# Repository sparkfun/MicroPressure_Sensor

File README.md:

# SparkFun MicroPressure Sensor

========================================

[*SparkFun MicroPressure Sensor (16476)*](https://www.sparkfun.com/products/16476)

<Basic description of the part.>

Repository Contents
-------------------

* **/Documentation** - Data sheets, additional product information
* **/Hardware** - Eagle design files (.brd, .sch)
* **/Libraries** - Libraries for use with the <PRODUCT NAME>
* **/Production** - Production panel files (.brd)
* **/Software** - Related software for the <PRODUCT NAME>

Documentation
-------------
* **[Library](https://github.com/sparkfun/SparkFun_MPR_Arduino_Library)** - Arduino library for the SparkFun MicroPressure Sensor.
* **[Hookup Guide](https://learn.sparkfun.com/tutorials/sparkfun-qwiic-micropressure-hookup-guide)** - Basic hookup guide for the SparkFun Qwiic MicroPressure Sensor.

License Information
-------------------

This product is _**open source**_! 

Please review the LICENSE.md file for license information. 

If you have any questions or concerns on licensing, please contact technical support on our [SparkFun forums](https://forum.sparkfun.com/viewforum.php?f=152).

Distributed as-is; no warranty is given.

- Your friends at SparkFun.

_<COLLABORATION CREDIT>_

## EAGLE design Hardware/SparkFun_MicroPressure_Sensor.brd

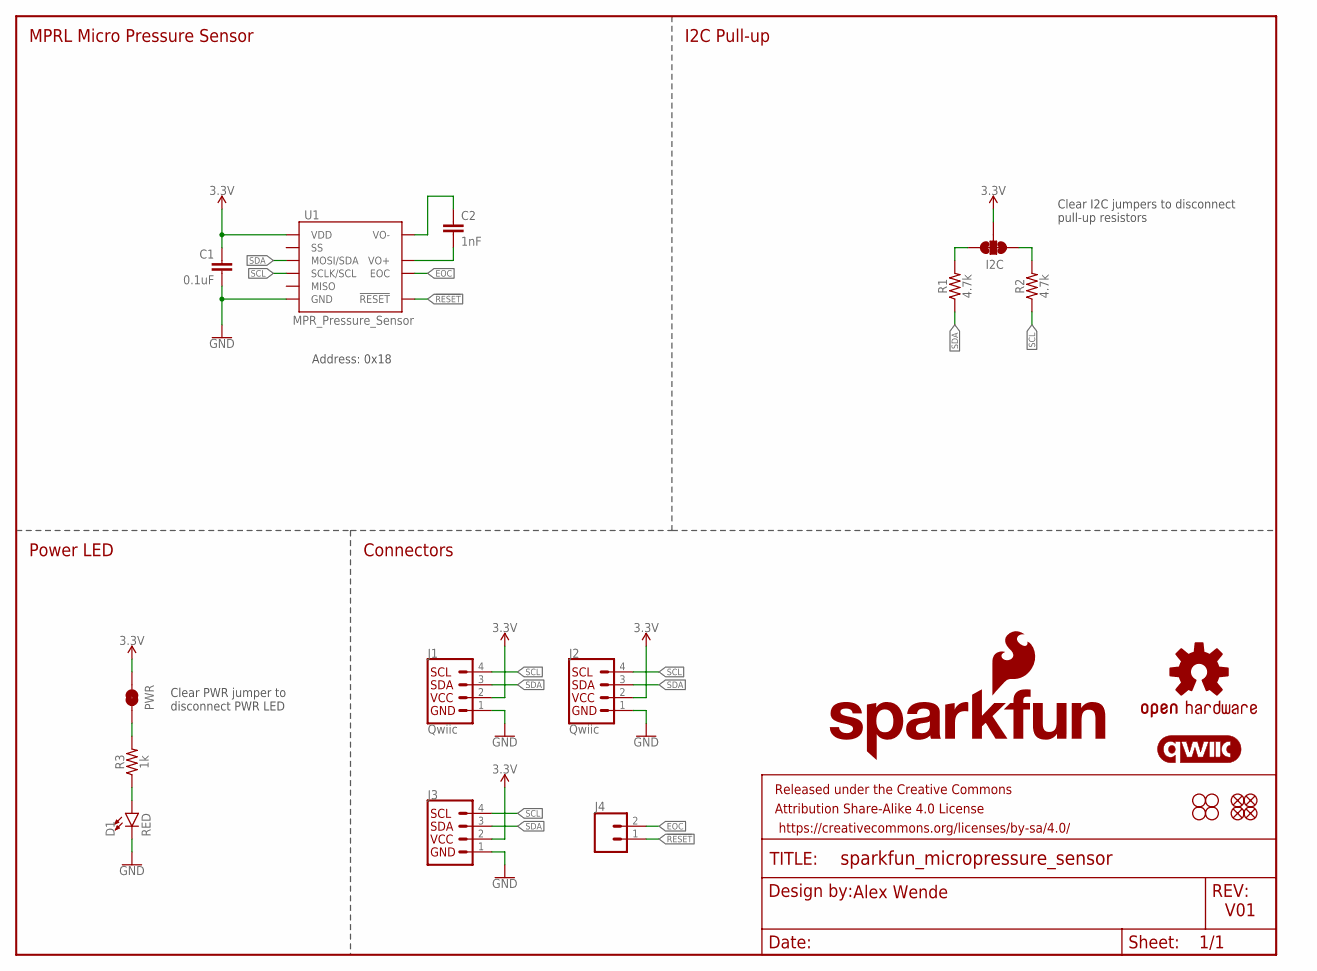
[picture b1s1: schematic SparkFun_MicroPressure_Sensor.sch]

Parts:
C1: 0.1uF; 0603
C2: 1nF; 0603
D1: RED; LED-0603
FD1, FD2, FD3, FD4: FIDUCIAL1X2; FIDUCIAL-1X2
FRAME1: FRAME-LETTER; CREATIVE_COMMONS
H1, H2, H3, H4: STAND-OFF
I2C: JUMPER-SMT_3_2-NC_TRACE_SILK; SMT-JUMPER_3_2-NC_TRACE_SILK
J1, J2: Qwiic; JST04_1MM_RA
J3: I2C_STANDARD_NO_SILK; 1X04_NO_SILK
J4: CONN_021X02_NO_SILK; 1X02_NO_SILK
LOGO1: QWIIC_LOGO_5MM; QWIIC_5MM
LOGO2: OSHW-LOGOS; OSHW-LOGO-S
LOGO3: SFE_LOGO_NAME_FLAME.1_INCH; SFE_LOGO_NAME_FLAME_.1
PWR: JUMPER-SMT_2_NC_TRACE_SILK; SMT-JUMPER_2_NC_TRACE_SILK
R1, R2: 4.7k; 0603
R3: 1k; 0603
U1: MPR_Pressure_Sensor; MPRL

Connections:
3.3V: C1.1, I2C.2, J1.2, J2.2, J3.2, PWR.1, U1.12 (VDD)
!RESET: J4.1, U1.9 (!RESET)
EOC: J4.2, U1.8 (EOC)
GND: C1.2, D1.C, J1.1, J2.1, J3.1, U1.10 (GND)
unnamed: PWR.2, R3.2
unnamed: D1.A, R3.1
unnamed: I2C.1, R2.2
unnamed: I2C.3, R1.2
unnamed: C2.2, U1.4 (VO+)
unnamed: C2.1, U1.6 (VO-)
SCL: J1.4, J2.4, J3.4, R2.1, U1.3 (SCLK/SCL)
SDA: J1.3, J2.3, J3.3, R1.1, U1.2 (MOSI/SDA)

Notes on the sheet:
MPRL Micro Pressure Sensor
Connectors
Power LED
I2C Pull-up
Clear I2C jumpers to disconnect pull-up resistors
Clear PWR jumper to disconnect PWR LED
V01
Alex Wende
Address: 0x18

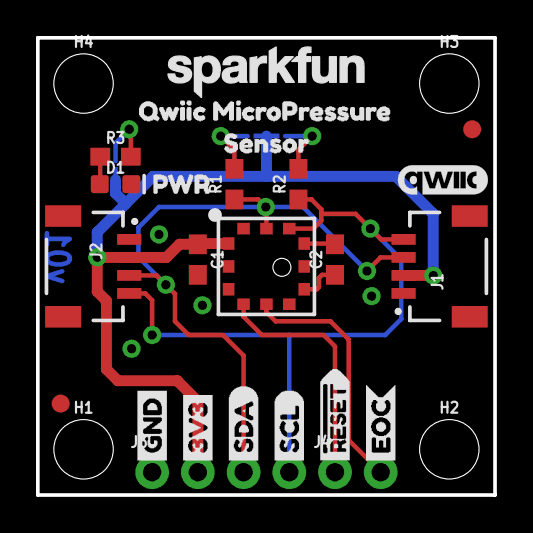
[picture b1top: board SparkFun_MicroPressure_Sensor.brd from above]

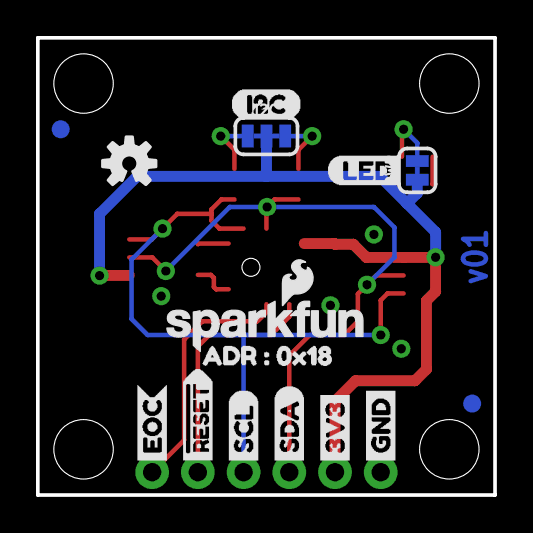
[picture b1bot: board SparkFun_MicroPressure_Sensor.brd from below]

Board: 2 copper layers, 25.4 x 25.4 mm, 44 parts (15 on the bottom side), 12 nets.

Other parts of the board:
U$1, U$15: GND1
U$2, U$14: 3V30
U$3, U$13: SDA2
U$4, U$12: SCL3
U$5, U$11: #RESET4
U$6, U$10: EOC5
U$7: PWR0
U$8: LED7
U$9: I2C6
U$16: QWIIC_MICROPRESSURE0
U$17: ADR_#_0X180
U$18: SENSOR2
U$19: SFE_LOGO_NAME_.1

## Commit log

2020-03-27 v01 Update
    - Added address to schematic, and pcb files
    - Rerouted 3.3V trace for better ground pour.
    - Updated MPR footprint silk

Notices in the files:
parts and their libraries:
SparkFun-Capacitors: Licensing: Creative Commons ShareAlike 4.0 International - https://creativecommons.org/licenses/by-sa/4.0
SparkFun-Aesthetics: Released under the Creative Commons Attribution Share-Alike 4.0 License
SparkFun-Aesthetics: https://creativecommons.org/licenses/by-sa/4.0
